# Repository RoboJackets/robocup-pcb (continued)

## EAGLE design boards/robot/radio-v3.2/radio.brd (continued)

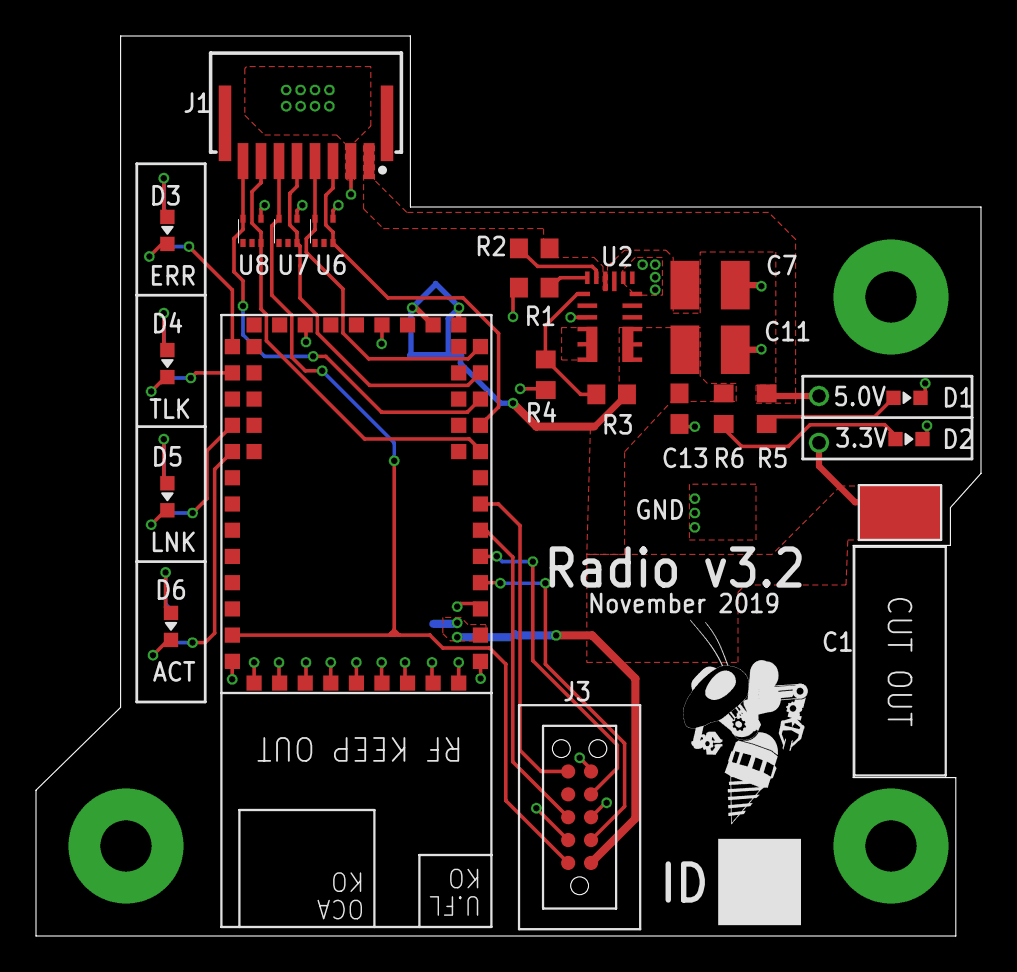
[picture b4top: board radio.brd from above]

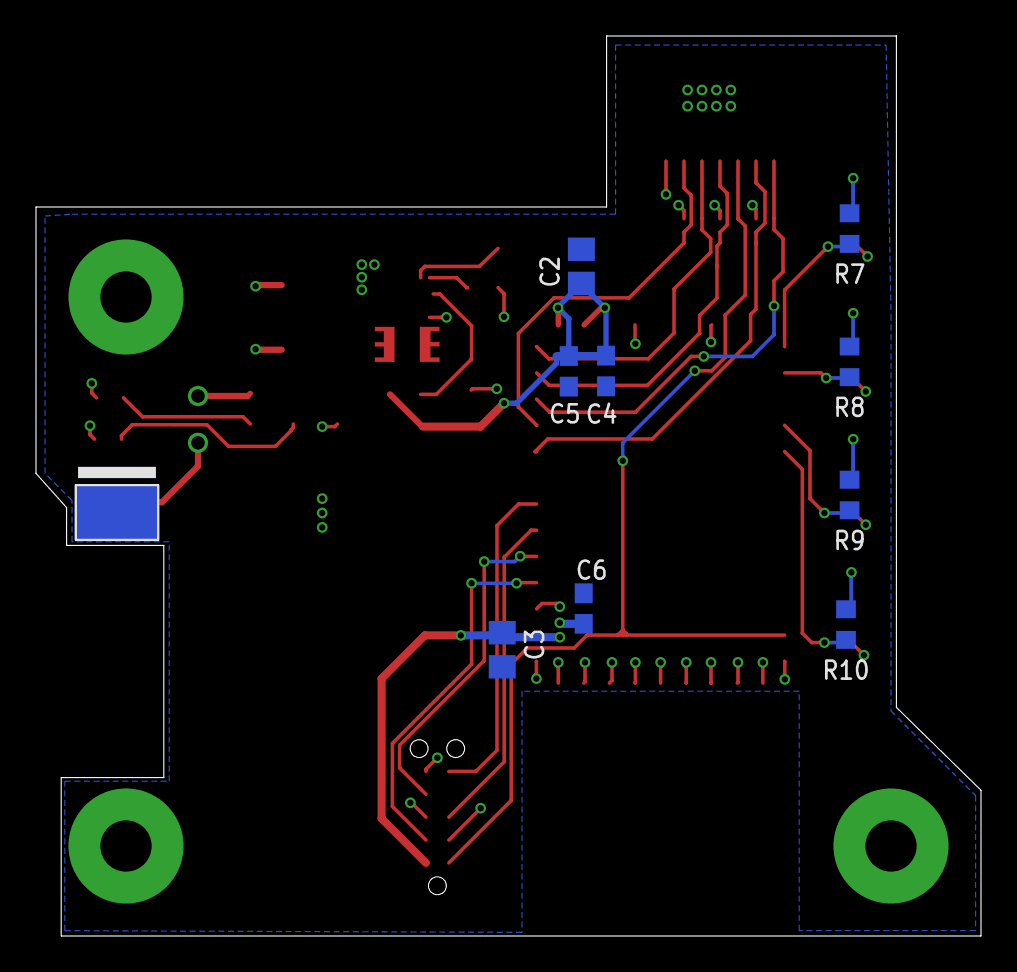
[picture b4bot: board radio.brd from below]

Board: 2 copper layers, 52.5 x 50.0 mm, 33 parts (9 on the bottom side), 26 nets.

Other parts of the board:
U$1: ROBOBUZZ_0.6X
